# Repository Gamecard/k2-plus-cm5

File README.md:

# K2 Plus CM5 – Creality K2 Plus mit Upstream-Klipper auf einem Raspberry Pi CM5

> **ALPHA – Stand 24.10.2026 – Nachbau und Betrieb auf eigene Gefahr.** Bisher an **einem** Drucker erprobt
> (Stock-Firmware 1.1.7.0). Unsichere Punkte sind in den Dokumenten mit **ANNAHME** bzw. **offen** markiert.

Dieses Repo ersetzt das Upper-Board des Creality K2 Plus (Allwinner T113 in der Display-Einheit) durch einen
**Raspberry Pi Compute Module 5 (CM5)** mit **Upstream-Klipper**, Moonraker und Mainsail. Bridge-Board, Mainboard,
Düsen-Platine, Closed-Loop-Motoren, CFS-Box und Riemen-Module bleiben im Gerät und behalten ihre
**Creality-Firmware**. Eigene Klipper-Module (`pi-host/k2_*.py`) sprechen deren Protokolle und bilden die
geschlossenen Creality-Teile nach:

- RS485-Bus (`k2_485`) mit Motor-Init (`k2_motor`), CFS-Box (`k2_box`), Riemenspannung (`k2_belt`),
- Kraftsensor-Antastung PrTouch (`k2_prtouch`) und Beschleunigungssensor (`k2_lis2dw`) über die Düsen-MCU,
- Sicherheits- und Komfortfunktionen des Creality-Hosts (`k2_safety`, `k2_chamber`, `k2_limits`,
  `k2_nozzle_tempcomp`, `k2_heater_pid`, `k2_zalign`, `k2_resume`, `k2_dateipruefung`, `k2_konsole`, `k2_cfs_sensor`).

Der Protokoll-Nachbau in Python liegt in `nachbau/`; der Installer kopiert ihn auf dem Pi nach
`~/klipper/klippy/extras/k2_nachbau/`. Bedient wird über Mainsail im Browser, das Original-Touchdisplay bleibt ohne
Funktion.

## Ziel des Projekts

**Der Creality K2 Plus soll mit Upstream-Klipper auf einem Raspberry Pi CM5 laufen – mit allen Funktionen des
Druckers, einschließlich CFS-Mehrfarbbetrieb.**

| Teil | Im Projekt |
|---|---|
| Upper-Board (Allwinner T113 in der Display-Einheit) | **ersetzt** durch den CM5 mit Upstream-Klipper, Moonraker und Mainsail |
| Bridge-Board, Mainboard, Düsen-Platine, Closed-Loop-Motoren, CFS-Box, Riemen-Module | **bleiben im Gerät**, mit ihrer originalen, unveränderten Creality-Firmware |
| Original-Touchdisplay | ohne Funktion; Bedienung über Mainsail im Browser, später optional ein eigenes DSI-Display |

**Software:** Damit Upstream-Klipper mit den verbleibenden Creality-Teilen zusammenarbeitet, bringt das Projekt eigene
Klipper-Module mit, die mit diesen Teilen kommunizieren und die Aufgaben übernehmen, die bisher der Creality-Host
erledigt hat:

- RS485-Bus, Motoren, CFS-Box und Riemenspannung (`k2_485`, `k2_motor`, `k2_box`, `k2_belt`),
- Kraftsensor-Antastung und Beschleunigungssensor über die Düsen-MCU (`k2_prtouch`, `k2_lis2dw`),
- Sicherheits- und Komfortfunktionen wie Fahrgrenzen, Kammer-Überwachung und Wiedereinstieg ab einer Schicht
  (`k2_safety`, `k2_chamber`, `k2_limits`, `k2_resume` u. a.).

**Hardware:** Die eigene Trägerplatine „K2-CM5-Träger Alpha 1“ sitzt an den Befestigungspunkten des T113, nimmt das
Original-Flachkabel auf und wird aus den 24 V des Druckers versorgt. Sie bringt RS485, CAN, Strommessung,
Stromausfall-Erkennung und Kamera-USB mit. Aus dem Aufbau mit IO-Board, Breakout und Steckbrücken wird so ein
sauberer Einbau.

**Was das bringt:**

- ein offenes, aktuelles Klipper statt eines festen Hersteller-Stands – eigene Makros, eigene Module, Mainsail,
  Kameras nach Wahl;
- Erweiterungen, die mit der Original-Software nicht möglich sind, z. B. CAN für einen späteren Toolhead;
- eine offene, nachbaubare Lösung für andere Besitzer eines K2 Plus.

**Ausblick (Idee, nicht begonnen):** eine Version 3 der Platine, die zusätzlich das Bridge-Board ersetzt – eine
eigene Platine statt T113, Bridge-Board und Adapter.

Das Projekt ist **Alpha**: Nachbau und Betrieb auf eigene Gefahr, Hardware nur für Testzwecke und nicht kommerziell
(CC BY-NC-SA 4.0, siehe [Lizenzen](#lizenzen)).

## Status

| Teil | Stand |
|---|---|
| Software (`pi-host/`, `nachbau/`) | läuft auf **CM5 + Waveshare CM5-IO-BASE-B** mit Breakout-Verdrahtung am Original-Flachkabel. Am Gerät erprobt (22.–23.10.2026): Klipper „ready“ mit beiden MCUs, Motor-Init, X/Y-Homing, Kraftsensor-Antastung, Bett ausrichten und Mesh, PID, Input Shaper, Riemenspannung, CFS-Laden/-Entladen/-Wechsel, einfarbiger Druck und ein Mehrfarbdruck (Creality-Print-7-Datei, 182 Wechsel) |
| Offen | u. a. Dual-Z-Lichtschranken, einige Druckfälle (PAUSE/RESUME, Restmaterial, Stall-Überwachung), `k2-bootstart` am Gerät – siehe [`SCHNELLSTART-K2-PLUS.md`](SCHNELLSTART-K2-PLUS.md) §9 und [`PI-INBETRIEBNAHME.md`](PI-INBETRIEBNAHME.md) Anhang D |
| Trägerplatine „K2-CM5-Träger Alpha 1“ (`hardware/k2-pi-cm5-traeger/`) | gefertigt, **seit 09.11.2026 an einem Drucker in Betrieb** (RS485, beide MCUs, CFS, Strommessung, CAN-Controller, Stromausfall-Erkennung, Kamera-USB geprüft); offen: DSI-Display, Ethernet, CAN mit Teilnehmer, Dauerlast-Temperatur – Details in der [Platinen-README](hardware/k2-pi-cm5-traeger/README.md) |
| Softwarepaket zur Trägerplatine (`pi-host/traeger-alpha1/`) | auf dem Träger installiert und **in Betrieb** (seit 09.11.2026) |

## Zwei Aufbauwege

**A – CM5 + IO-Board + Verdrahtung (heute erprobt).** CM5 auf einem IO-Board mit 40-Pol-Leiste (bei uns Waveshare
CM5-IO-BASE-B), FFC-Breakout am Original-Flachkabel, vier UART-Leitungen mit 1 kΩ, USB-RS485-Adapter für den Bus.

1. [`SCHNELLSTART-K2-PLUS.md`](SCHNELLSTART-K2-PLUS.md) – der Weg vom unveränderten Drucker bis zum Druck, kurz gefasst;
   Verkabelung in Abschnitt 3, Verdrahtungsbild: [`bilder/verdrahtung-weg-a.png`](bilder/verdrahtung-weg-a.png).
2. [`PI-ANSCHLUSS-LOWERBOARD.md`](PI-ANSCHLUSS-LOWERBOARD.md) – Bridge-Board, J14-/J22-Belegung, Messprotokoll.
3. [`PI-INBETRIEBNAHME.md`](PI-INBETRIEBNAHME.md) – Fahrplan Phase 0–12 mit Erwartungswerten, Not-Aus-Stufen,
   Schalterstand und Rückweg zum Original.

**B – Trägerplatine (Alpha, seit 09.11.2026 an einem Drucker in Betrieb).** Der Träger sitzt an den Befestigungspunkten des T113, trägt den CM5
direkt und nimmt das Original-Flachkabel auf; versorgt wird er aus den 24 V des Druckers. Breakout, Steckbrücken und
USB-RS485-Adapter entfallen.

1. [`hardware/k2-pi-cm5-traeger/README.md`](hardware/k2-pi-cm5-traeger/README.md) – Platine, Einkauf, Aufbau und Inbetriebnahme
   ([`AUFBAU-UND-INBETRIEBNAHME.md`](hardware/k2-pi-cm5-traeger/AUFBAU-UND-INBETRIEBNAHME.md)).
2. [`pi-host/traeger-alpha1/README-traeger-alpha1.md`](pi-host/traeger-alpha1/README-traeger-alpha1.md) –
   Softwarepaket und Umstieg (RS485 über UART0, CAN, Stromausfall-Wächter, `config.txt`).

## Einstieg

Mit [`SCHNELLSTART-K2-PLUS.md`](SCHNELLSTART-K2-PLUS.md) anfangen. Vor dem Umbau am **laufenden Original** die
Kalibrierwerte, die Materialdatenbank und das Düsenmaterial sichern (Schnellstart §2) – diese Dateien enthalten
Geräte- und Cloud-Kennungen und gehören **nie** in ein Repo oder Paket.

Kurzform der Installation (Einzelheiten: [`pi-host/install/README.md`](pi-host/install/README.md)):

```bash
git clone https://github.com/Gamecard/k2-plus-cm5.git
cd k2-plus-cm5
pi-host/install/pack.sh --tests --ohne-dicts      # oder --dicts ORDNER mit den MCU-Dictionaries der Creality-Firmware
scp lokal/pi-paket/k2-pi-paket-<datum>.tar.gz pi@<pi-ip>:~
ssh pi@<pi-ip>
tar xzf k2-pi-paket-<datum>.tar.gz && cd k2-pi-paket-<datum>
./install.sh --printer-cfg-ersetzen --bewegung-gesperrt   # weitere Optionen: Schnellstart §4
```

Der Ordner `lokal/` ist git-ignoriert und nimmt alles Gerätebezogene auf (gebaute Pakete, MCU-Dictionaries, optional
eine eigene Leak-Muster-Liste für `pack.sh`).

## Ordnerübersicht

| Pfad | Inhalt |
|---|---|
| [`SCHNELLSTART-K2-PLUS.md`](SCHNELLSTART-K2-PLUS.md) | Einstieg: Voraussetzungen, Sichern, Verkabelung, Installation, Kalibrierung, Slicer, Betrieb, Rückweg |
| [`PI-ANSCHLUSS-LOWERBOARD.md`](PI-ANSCHLUSS-LOWERBOARD.md) | Anschluss an Bridge- und Mainboard, Messwerte, Belegungen |
| [`PI-INBETRIEBNAHME.md`](PI-INBETRIEBNAHME.md) | Fahrplan der Inbetriebnahme (Phase 0–12, Anhänge Rückweg, Protokoll, Variante A) |
| [`BOOTSTART-WERKZEUG.md`](BOOTSTART-WERKZEUG.md) | `k2-bootstart`: Geräte aus dem Bootloader in die App starten (Gerätetest offen, Standard aus) |
| [`pi-host/`](pi-host/README.md) | Klipper-Module `k2_*.py`, Offline-Tests `test_k2_*.py`, je Modul eine `README-k2_*.md` |
| [`pi-host/config-pi/`](pi-host/config-pi/README.md) | Klipper-Konfiguration des K2 Plus (`printer.cfg`, Makros, Module, Homing, Z-Ausrichtung) mit Bedienhinweisen |
| [`pi-host/install/`](pi-host/install/README.md) | `pack.sh` (Paket bauen), `install.sh`/`uninstall.sh`, `k2-identify.py`, `k2-bootstart.py`, Start-Wächter, Creality-Brücke, Web-Anpassungen, Tests |
| [`pi-host/traeger-alpha1/`](pi-host/traeger-alpha1/README-traeger-alpha1.md) | Softwarepaket für die Trägerplatine (am Träger in Betrieb) |
| `nachbau/` | Python-Nachbau der Creality-Protokolle (RS485-Bus, CFS-Box, Motoren, Adressvergabe, Bootstart, Spülen, Materialdatenbank); `ref-hi/` = Testvektoren |
| [`hardware/k2-pi-cm5-traeger/`](hardware/k2-pi-cm5-traeger/README.md) | Trägerplatine Alpha 1: Generator, KiCad-Projekt, Fertigungsdaten in `ausgabe/`, Bestell- und Aufbauanleitung |
| [`hardware/LIZENZ-UND-HAFTUNG.md`](hardware/LIZENZ-UND-HAFTUNG.md) | Lizenz (CC BY-NC-SA 4.0) und Haftungsausschluss der Hardware |
| `belt_mdl-live.py` | Creality-Original des Riemenmoduls (GPLv3), Vergleichsreferenz für `pi-host/test_k2_belt.py` |
| [`NOTICES.md`](NOTICES.md), [`LICENSE`](LICENSE) | Herkunfts- und Lizenzhinweise, GPL-3.0 |

## Sicherheit und Verbote

**Was dieses Projekt nie tut – und was auch Nutzer nicht tun sollten:**

- **Keine Motor-Kalibrierung:** Die Motor-Schreibbefehle **0x03** (Encoder), **0x04** (Elektrik-Offset) und
  **0x07** (Flash-Parameter) sind im Sendeschutz gesperrt. Den Sendeschutz nicht umgehen.
- **Kein Bootloader-Einstieg und kein Flashen** von Motoren, CFS, Riemen-Modulen oder MCUs (u. a. `FF 0B [00]`,
  fun 0xF0 Sub 01, `mcu_util`-/`mcu_util_485`-/SWD-Wege) und **kein CFS-DB-Erase** (`F0 [06]`). `k2-bootstart`
  startet nur, es aktualisiert nie.
- **Main-MCU (Lower-Board) und Düsen-MCU NICHT mit generischem Klipper flashen.** Die Module sind auf die originale
  Creality-MCU-Firmware abgestimmt (erprobt: `1.1.0.48-293-g493f9a0f`). Weil nichts geflasht wird, bleibt der
  Rückweg zum Original jederzeit möglich (Flachkabel zurück an das T113).

**Elektrik und Mechanik:**

- Arbeiten an 24 V und an der Drucker-Elektronik erfolgen **auf eigene Gefahr**. Auf dem Bridge-Board liegen
  RS232-Pegel von ±5,5 V, die Pi-UARTs vertragen höchstens 3,3 V. Stecken und Ziehen nur bei ausgeschaltetem Drucker
  **und** Pi, GND zuerst. Die 5-V-Stifte des Breakouts nie an den Pi.
- Ab der Bewegungsfreigabe kann der Kopf in den Rahmen, die Düse ins Bett fahren: immer eine Person am Netzschalter,
  Bett leer. Bus-Schreiben und Bewegung sind ab Werk gesperrt (`allow_write`/`allow_move`) und werden schrittweise
  nach dem Fahrplan freigegeben.
- Die Heizungen gehen **nie automatisch** aus (`[idle_timeout]` wie Stock): nach jedem Heizschritt
  `TURN_OFF_HEATERS`.
- Der Eingriff kann Garantie- bzw. Gewährleistungsansprüche gegenüber dem Hersteller beeinträchtigen. Es gibt keine
  Gewährleistung und keinen Support.

## Lizenzen

- **Software** (`pi-host/`, `nachbau/`, Skripte, Dokumentation außerhalb von `hardware/`): **GPL-3.0-or-later**
  ([`LICENSE`](LICENSE)). Die Module sind Erweiterungen für Klipper (GPL-3.0).
- `belt_mdl-live.py` ist ein **Creality-Original** unter **GPLv3** (Lizenzhinweis im Dateikopf).
- `nachbau/ref-hi/` stammt aus **gitstonelabs/creality-cfs-klipper** (GPL-3.0).
- **Hardware** (`hardware/`): **CC BY-NC-SA 4.0**, Alpha, nur für Testzwecke, keine kommerzielle Nutzung –
  Einzelheiten und Haftungsausschluss in [`hardware/LIZENZ-UND-HAFTUNG.md`](hardware/LIZENZ-UND-HAFTUNG.md).
- Weitere Herkunftsangaben: [`NOTICES.md`](NOTICES.md).

## Hinweis

Dieses Projekt ist unabhängig und **nicht mit Creality verbunden**. „Creality“, „K2 Plus“, „CFS“, „Raspberry Pi“
und alle anderen genannten Marken gehören ihren jeweiligen Inhabern.

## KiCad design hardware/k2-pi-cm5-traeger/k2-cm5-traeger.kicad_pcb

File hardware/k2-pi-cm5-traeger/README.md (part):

# K2-CM5-Träger Alpha 1 (Weg B) – Layout-Entwurf (23.10.2026, Umbau 24.10.2026)

> **ALPHA – NUR FÜR TESTZWECKE – NICHT FÜR DEN KOMMERZIELLEN EINSATZ – NUTZUNG AUF EIGENE GEFAHR.**
> Lizenz und Haftungsausschluss: siehe [`../LIZENZ-UND-HAFTUNG.md`](../LIZENZ-UND-HAFTUNG.md).

> **Status (11.11.2026): Alpha 1 – gefertigt (JLC), seit 09.11.2026 an einem Drucker in Betrieb.** Layout
> DRC/ERC 0 Fehler. Am Gerät geprüft: Versorgung aus den 24 V des Druckers, beide MCUs über das Original-Flachkabel, RS485 über den Treiber der Platine (Motor-Init aller fünf Motoren, CFS-Box), Strommessung (INA226 24 V und 5 V), CAN-Controller erkannt, Stromausfall-Erkennung, beide Kamera-USB, erste Drucke mit CFS-Wechsel. **Offen:** DSI-Display (Hintergrundlicht/Touch antworten nicht, Ursache offen), Ethernet, CAN mit angeschlossenem Teilnehmer, CM5-Temperatur unter Dauerlast (passiver Kühler, bisher 63–66 °C, keine Drosselung).
> Weitere Punkte: [Offene Punkte](#offene-punkte) am Ende.

> **Unterlagen:** [Fertigungshinweise](#fertigungshinweise-leiterplatte-und-bestückung) · [`EINKAUFSLISTE.md`](EINKAUFSLISTE.md) (alles außer JLC) · [`AUFBAU-UND-INBETRIEBNAHME.md`](AUFBAU-UND-INBETRIEBNAHME.md)
> (Messungen in 12 Etappen) · [`KOMPROMISSE-UND-OFFENE-PUNKTE.md`](KOMPROMISSE-UND-OFFENE-PUNKTE.md) · Software:
> [`../../pi-host/traeger-alpha1/README-traeger-alpha1.md`](../../pi-host/traeger-alpha1/README-traeger-alpha1.md).

> **Umbau 24.10.2026 (Nutzerwunsch):** 24-V-Eingang **J7 an Kante A** (über J1, Kabel von links wie beim Flachkabel),
> **J9b/J11 stehend** (JST GH Top entry), **tauschbare Eingangssicherung** (Littelfuse 157 mit Nano²-Sicherung),
> **Stromausfall-Erkennung** (INA226-ALERT → GPIO27).

> **Weg A (Entscheidung 24.10.2026):** **J9 (Toolhead 24 V + CAN) entfällt** samt eFuse, INA226 0x44 und dem
> 24-V-Stamm quer über die Platine. Der Toolhead bekommt seine 24 V **direkt vom Drucker-Netzteil** (eigene Kabelsicherung
> ≈ 5 A, siehe „Toolhead-Versorgung“), CAN läuft über **J9b**. Eingangssicherung **F1 jetzt 3 A** (Platine braucht ≈ 10–15 W).
> Die Platzhalter-Quader der 3D-Ansicht sind, wo möglich, durch echte Modelle ersetzt (siehe „3D-Modelle und Lizenzen“).

Konzept und Begründungen: [`KONZEPT.md`](KONZEPT.md) (inkl. Tabelle „Entscheidungen“).

## Zweck

Der Träger ersetzt das T113-Upper-Board des K2 Plus an dessen vier Befestigungspunkten. Er trägt ein **Raspberry Pi
Compute Module 5 (CM5)** direkt (zwei 100-pol. Steckverbinder, 1,5 mm Bauhöhe) – ohne IO-Board. Das Original-Flachkabel
vom Bridge-Board steckt in **J1** (Lage wie CON2 der T113). Der Träger versorgt den CM5 selbst aus den 24 V des Druckers.

## Funktionen

| Block | Umsetzung | Anschluss / CM5-Pins |
|---|---|---|
| Flachkabel J1 | 50-pol. FPC 0,5 mm (XUNPU FPC-05FB-50PH20), Kante A; J1-Pin n = Breakout-Nummer n (CON2 = 51 − Breakout) | Breakout 45–50 = Drucker-5V (**nie** am CM5-5V), 1/2 + 4/5 Ethernet |
| UART2 / UART4 | je 1 kΩ + ESD (SRV05-4) + Ioff-Puffer SN74LVC1G125 (5,5-V-tolerant) | Breakout 26/28 (UART2), 30/32 (UART4); CM5 54/34, 31/28 |
| RS485 | THVD1450 an UART0, DE = GPIO17; Ruhevorspannung (JP2/JP3) und 120 Ω (JP_485_TERM) schaltbar | Breakout 19 = B, 20 = A; CM5 55/51/50 |
| RS485-Abgriff J11 | JST GH 3-pol. **stehend** (BM03B-GHS-TBT, LCSC C161691), A/B/GND parallel zum Bus, ESD | Kante D |
| CAN | MCP2518FD (SPI0, INT = GPIO25) + SN65HVD230, ESD NUP2105 | CM5 44/40/38/39/41 |
| **CAN-Anschluss J9b** | JST GH 3-pol. **stehend** (BM03B-GHS-TBT, LCSC C161691): CANH, CANL, GND (kein 24 V) – seit Weg A **der** CAN-Anschluss für ein späteres Toolhead-Board (24 V dafür direkt vom Netzteil) | **Kante B** (zwischen L-Spule und L2) |
| CAN-Abschluss | 120 Ω über Stiftleiste **JP_CAN_TERM** („CAN 120R“), Jumper **ab Werk gesteckt** | Kante D unten rechts |
| 24-V-Eingang J7 | XT30PW-M liegend (Stecköffnung nach links), **tauschbare Sicherung F1** (Littelfuse 157, **3 A**), TVS D8, Shunt R23 5 mΩ + INA226 0x40 direkt dahinter (unten, unter J7), 24-V-Stamm auf L3 nur noch bis zum Wandler | **Kante A oben** (über J1) |
| Stromausfall-Erkennung | INA226 0x40 ALERT (open drain) → **PWR_FAIL_N** → **GPIO27 (CM5-Pin 48)**, 10 k Pull-up R50, Messpad TP12 | siehe unten |
| 5,2 V für den CM5 | LMR51450 (5 A, Spule FXL0630) → Power-Mux TPS2121 → Shunt 10 mΩ (INA226 0x41) → CM5 77–87 | – |
| Notfall-USB-C J10 | stehend, Kante B bei L1: USB-OTG (CM5 103/105), CC 94/96 (5,1 k als Bestückoption), nRPIBOOT per Jumper **JP_BOOT**, 5 V über TPS2121, ESD USBLC6 | USB_OTG_ID 101 offen |
| Kamera-/Hub-USB | 90 Ω, CM5 134/136 bzw. 163/165 → J1 37/38 bzw. 34/35, ESD | – |
| Ethernet | CM5-Paar 0 (12/10) und 1 (4/6) → eigener Übertrager H1102NL → J1 1/2 und 4/5, Mittelanzapfung/Bob-Smith | – |
| **DSI-Display J12** | **bestückt**: 22-pol. FPC 0,5 mm Hirose FH12-22S-0.5SH(55), Belegung wie Raspberry Pi 5 / CM-IO; **MIPI1 = DSI1**, 2 Datenlanes + Takt | **Kante C** (wie CON1 der T113) |
| DSI-3,3 V | eigener Abwärtswandler TLV62569 (2 A) aus CM5-5V, EN an CM5-3,3V | J12 Pin 22 |
| LEDs | 3V3, nACT (21), Ethernet nLED3/nLED2 (15/17), D10 „Flachkabel richtig“ (Drucker-5V) | Kante D |
| Messpunkte | 5V, 3V3, RUN (99), BOOT (93), PWR (92), GND; unten 24 V, BR_5V, PWR_FAIL (TP12) | Kante D bzw. unten |
| Sonstiges | GPIO_VREF (78) an 3,3 V, EEPROM_nWP (20) offen; **GPIO6 (30) und GPIO26 (24) frei** (seit Weg A, im Schaltplan als „frei“ vermerkt) | – |

## DSI-Display (Nachtrag 2/3)

- Ziel-Display: **Waveshare 4.3inch DSI LCD** (800 × 480, Touch Goodix über I2C im Kabel, 3,3 V ≈ 1,2 W, Kabel 22 → 15 pol.).
  Für Pi 5/CM5 ist **Rev 2.2** des Displays nötig (Tabelle „Entscheidungen“ in `KONZEPT.md`).
- Stecker **J12 an Kante C**, senkrecht entlang der Kante zwischen den Bohrungen L2 und L4, Öffnung zur Kante, Kabel geht
  nach außen ab – dort, wo an der T113 der Display-Stecker **CON1** sitzt (am 23.10.2026 bestätigt).
- Kontaktseite und Pin 1 wie Raspberry Pi 5 bzw. CM-IO-Board: Es ist **derselbe Stecker (Hirose FH12-22S-0.5SH)** wie auf dem
  CM4-IO-Board (KiCad-Designdaten von Raspberry Pi), Pin 1 liegt am südlichen Ende (Richtung L4). Ein Pi-5-Displaykabel passt
  ohne Verdrehen.
- Belegung (wie Pi 5 / CM-IO, 22-pol.):

| Pin | Signal | CM5-Pin | Pin | Signal | CM5-Pin |
|---|---|---|---|---|---|
| 1 | GND | – | 12 | D2_P | nicht verlegt (offen) |
| 2 | D0_N | 175 (MIPI1_D0_N) | 13 | GND | – |
| 3 | D0_P | 177 | 14 | D3_N | nicht verlegt (offen) |
| 4 | GND | – | 15 | D3_P | nicht verlegt (offen) |
| 5 | D1_N | 181 | 16 | GND | – |
| 6 | D1_P | 183 | 17 | CAM_GPIO0 | 97 |
| 7 | GND | – | 18 | CAM_GPIO1 | 100 |
| 8 | C_N | 187 (MIPI1_C_N) | 19 | GND | – |
| 9 | C_P | 189 | 20 | SCL | 35 (ID_SC), 2,2 k nach 3,3 V |
| 10 | GND | – | 21 | SDA | 36 (ID_SD), 2,2 k nach 3,3 V |
| 11 | D2_N | nicht verlegt (offen) | 22 | 3,3 V | DSI-Wandler U14 |

- Port-Wahl: **MIPI1 (DSI1)**, weil seine Pins (175–189) in Reihe B direkt zur rechten Kante zeigen; die I2C von MIPI1 liegt
  laut CM5-Datenblatt auf **ID_SD/ID_SC (Pin 36/35)**. Software: `dtoverlay=vc4-kms-dsi-7inch` (= DSI1). Für DSI0 wäre es
  `dtoverlay=vc4-kms-dsi-7inch,dsi0` – auf diesem Träger **nicht** verdrahtet.
- Paare: Takt, D0, D1 als **100-Ω-Paare 0,20/0,20 mm** nur auf L1 über der GND-Lage, ohne Via; Länge je Leitung
  **49,870 mm**, Abweichung im Paar und zwischen den Lanes < 0,001 mm (verschachtelte Paarbeulen + Innenabgleich).
  D2/D3 sind nicht verlegt – das Waveshare-Kabel (15-pol. Ende) führt ohnehin nur 2 Lanes.
- **3,3-V-Budget:** eigener Abwärtswandler **TLV62569** (2 A, 1,5 MHz, 2,2 µH, 2 × 22 µF) aus CM5-5V; Bedarf des Displays
  ≈ 1,2 W ≈ 0,36 A ≥ 0,5 A Vorgabe ✓ (2 A Reserve). Er belastet die 5,2-V-Schiene mit ≈ 0,3 A. Die 3,3-V-Schiene des CM5
  wird nicht belastet (sie schaltet nur EN, damit das Display nicht in einen ausgeschalteten CM5 zurückspeist).

## Mechanik und Lage

Draufsicht von oben, Ursprung linke obere Ecke, x nach rechts, y nach unten, Maße in mm.

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
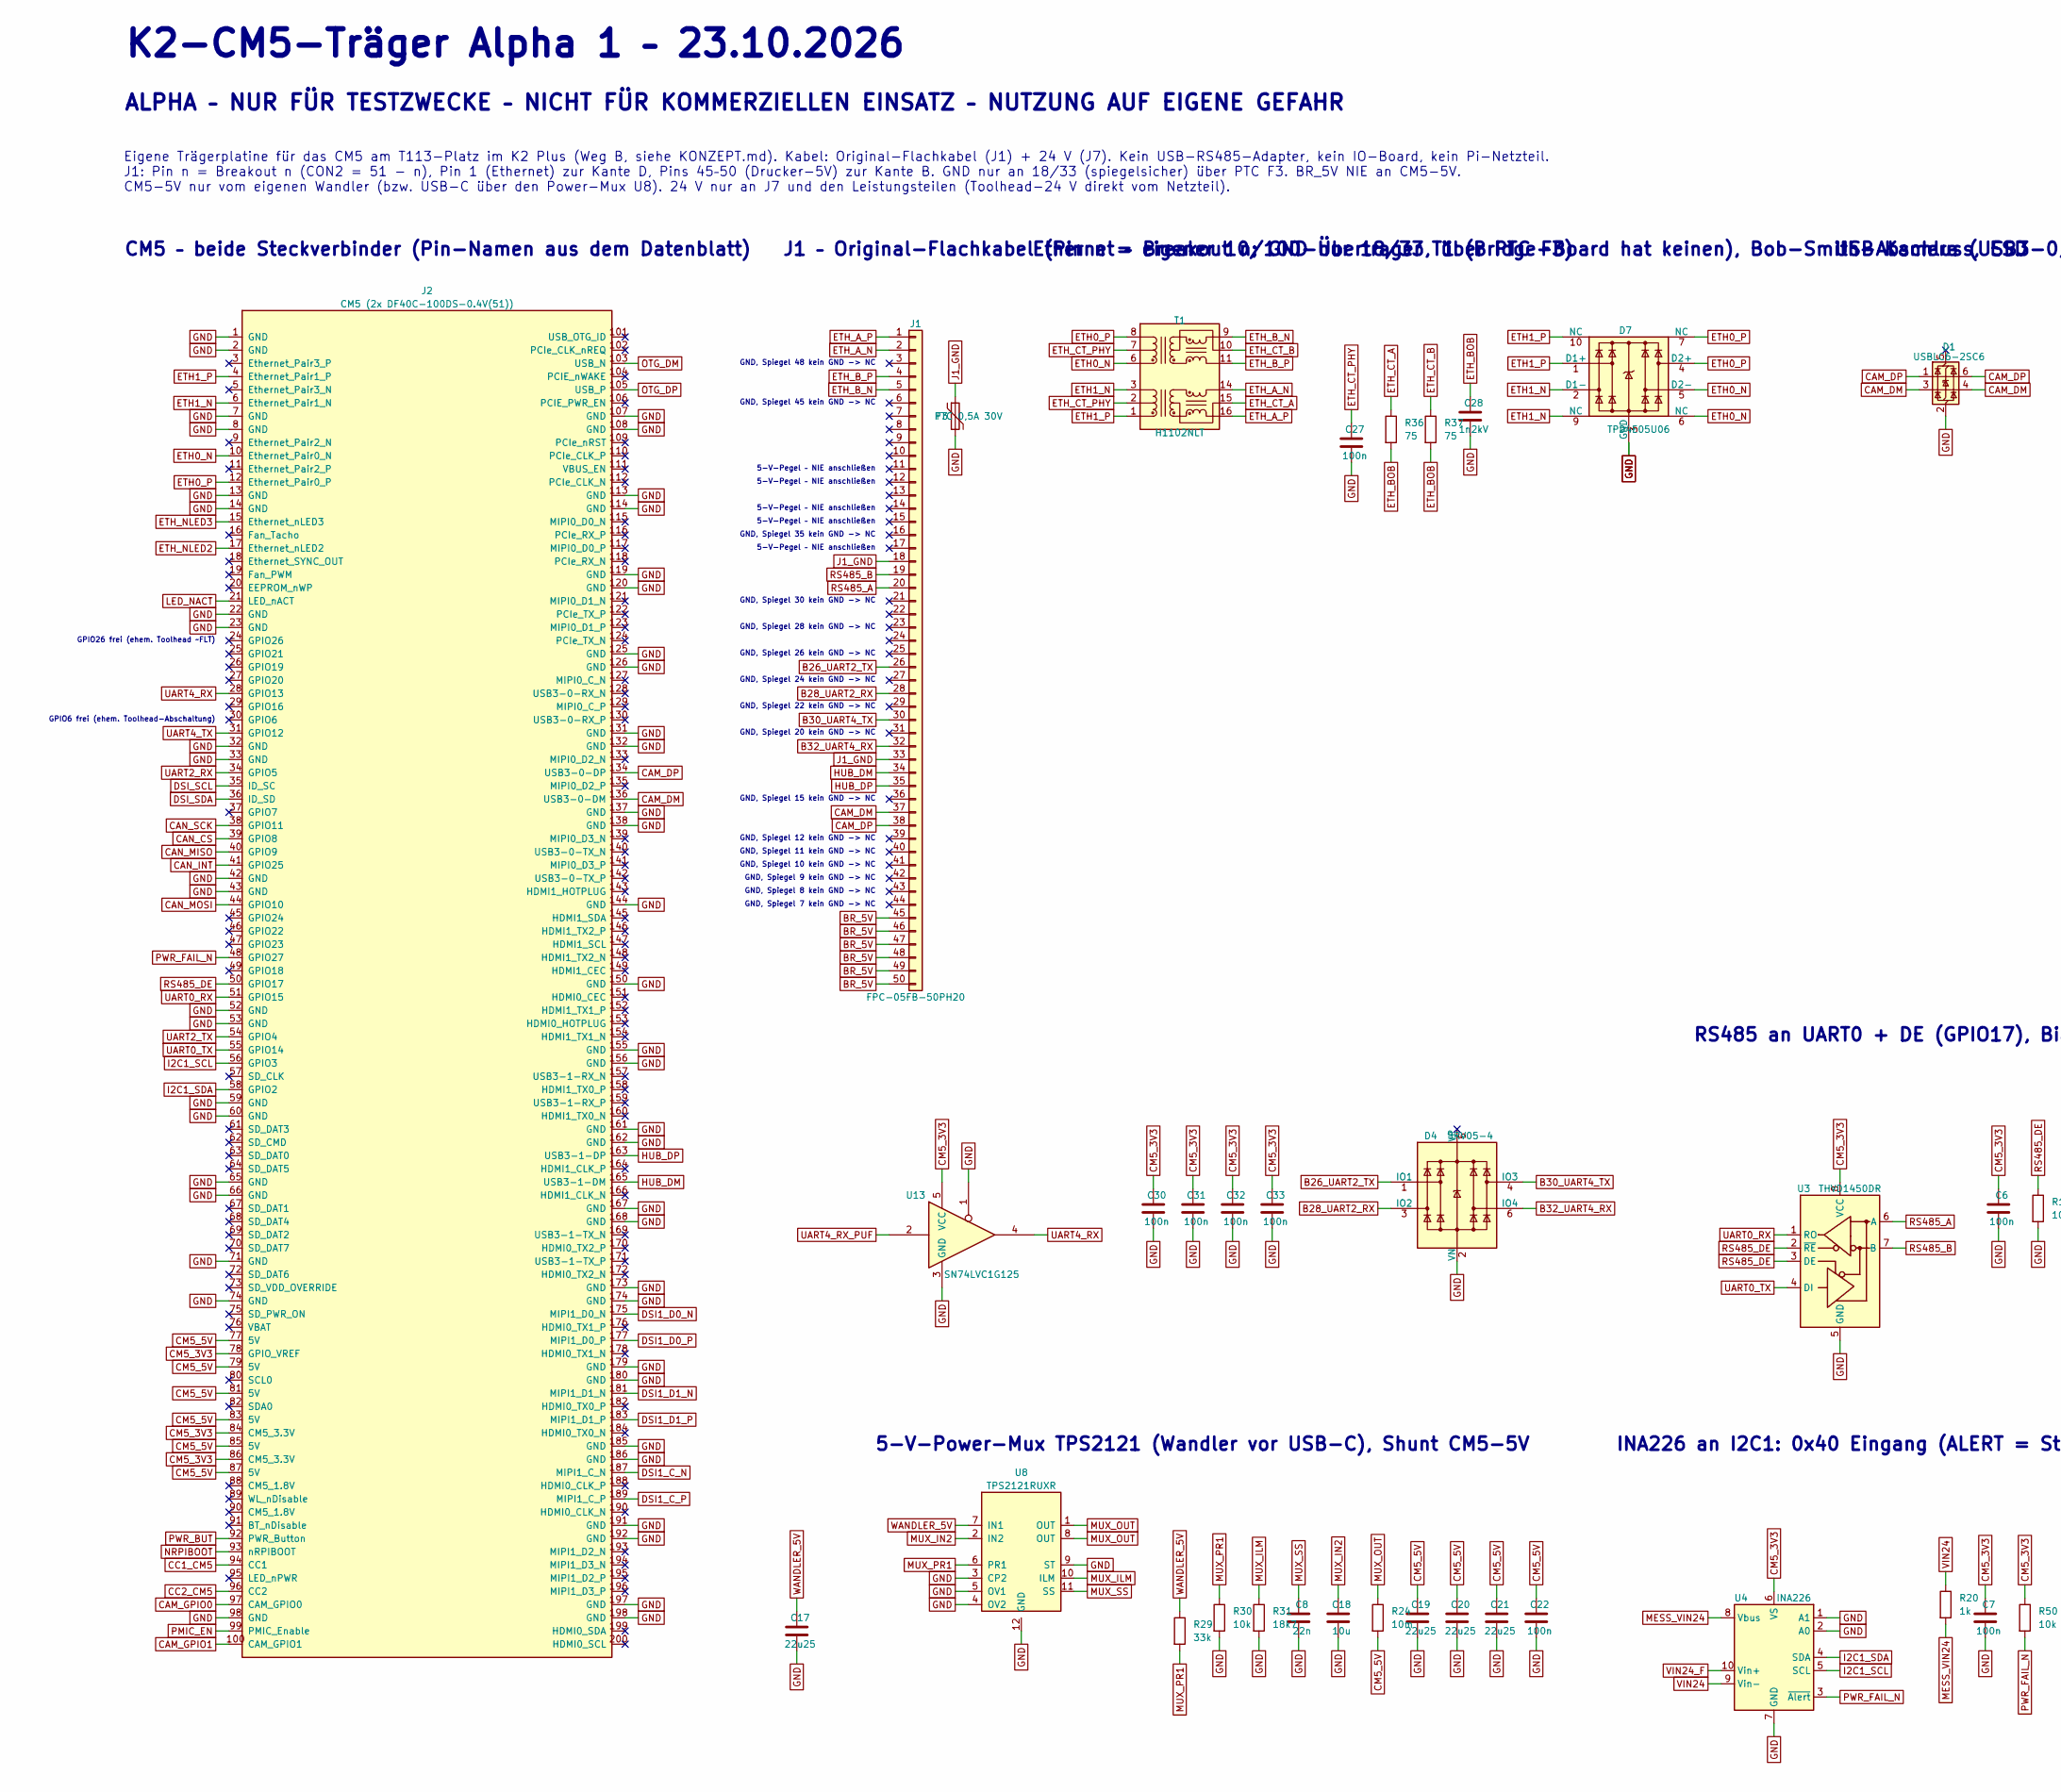
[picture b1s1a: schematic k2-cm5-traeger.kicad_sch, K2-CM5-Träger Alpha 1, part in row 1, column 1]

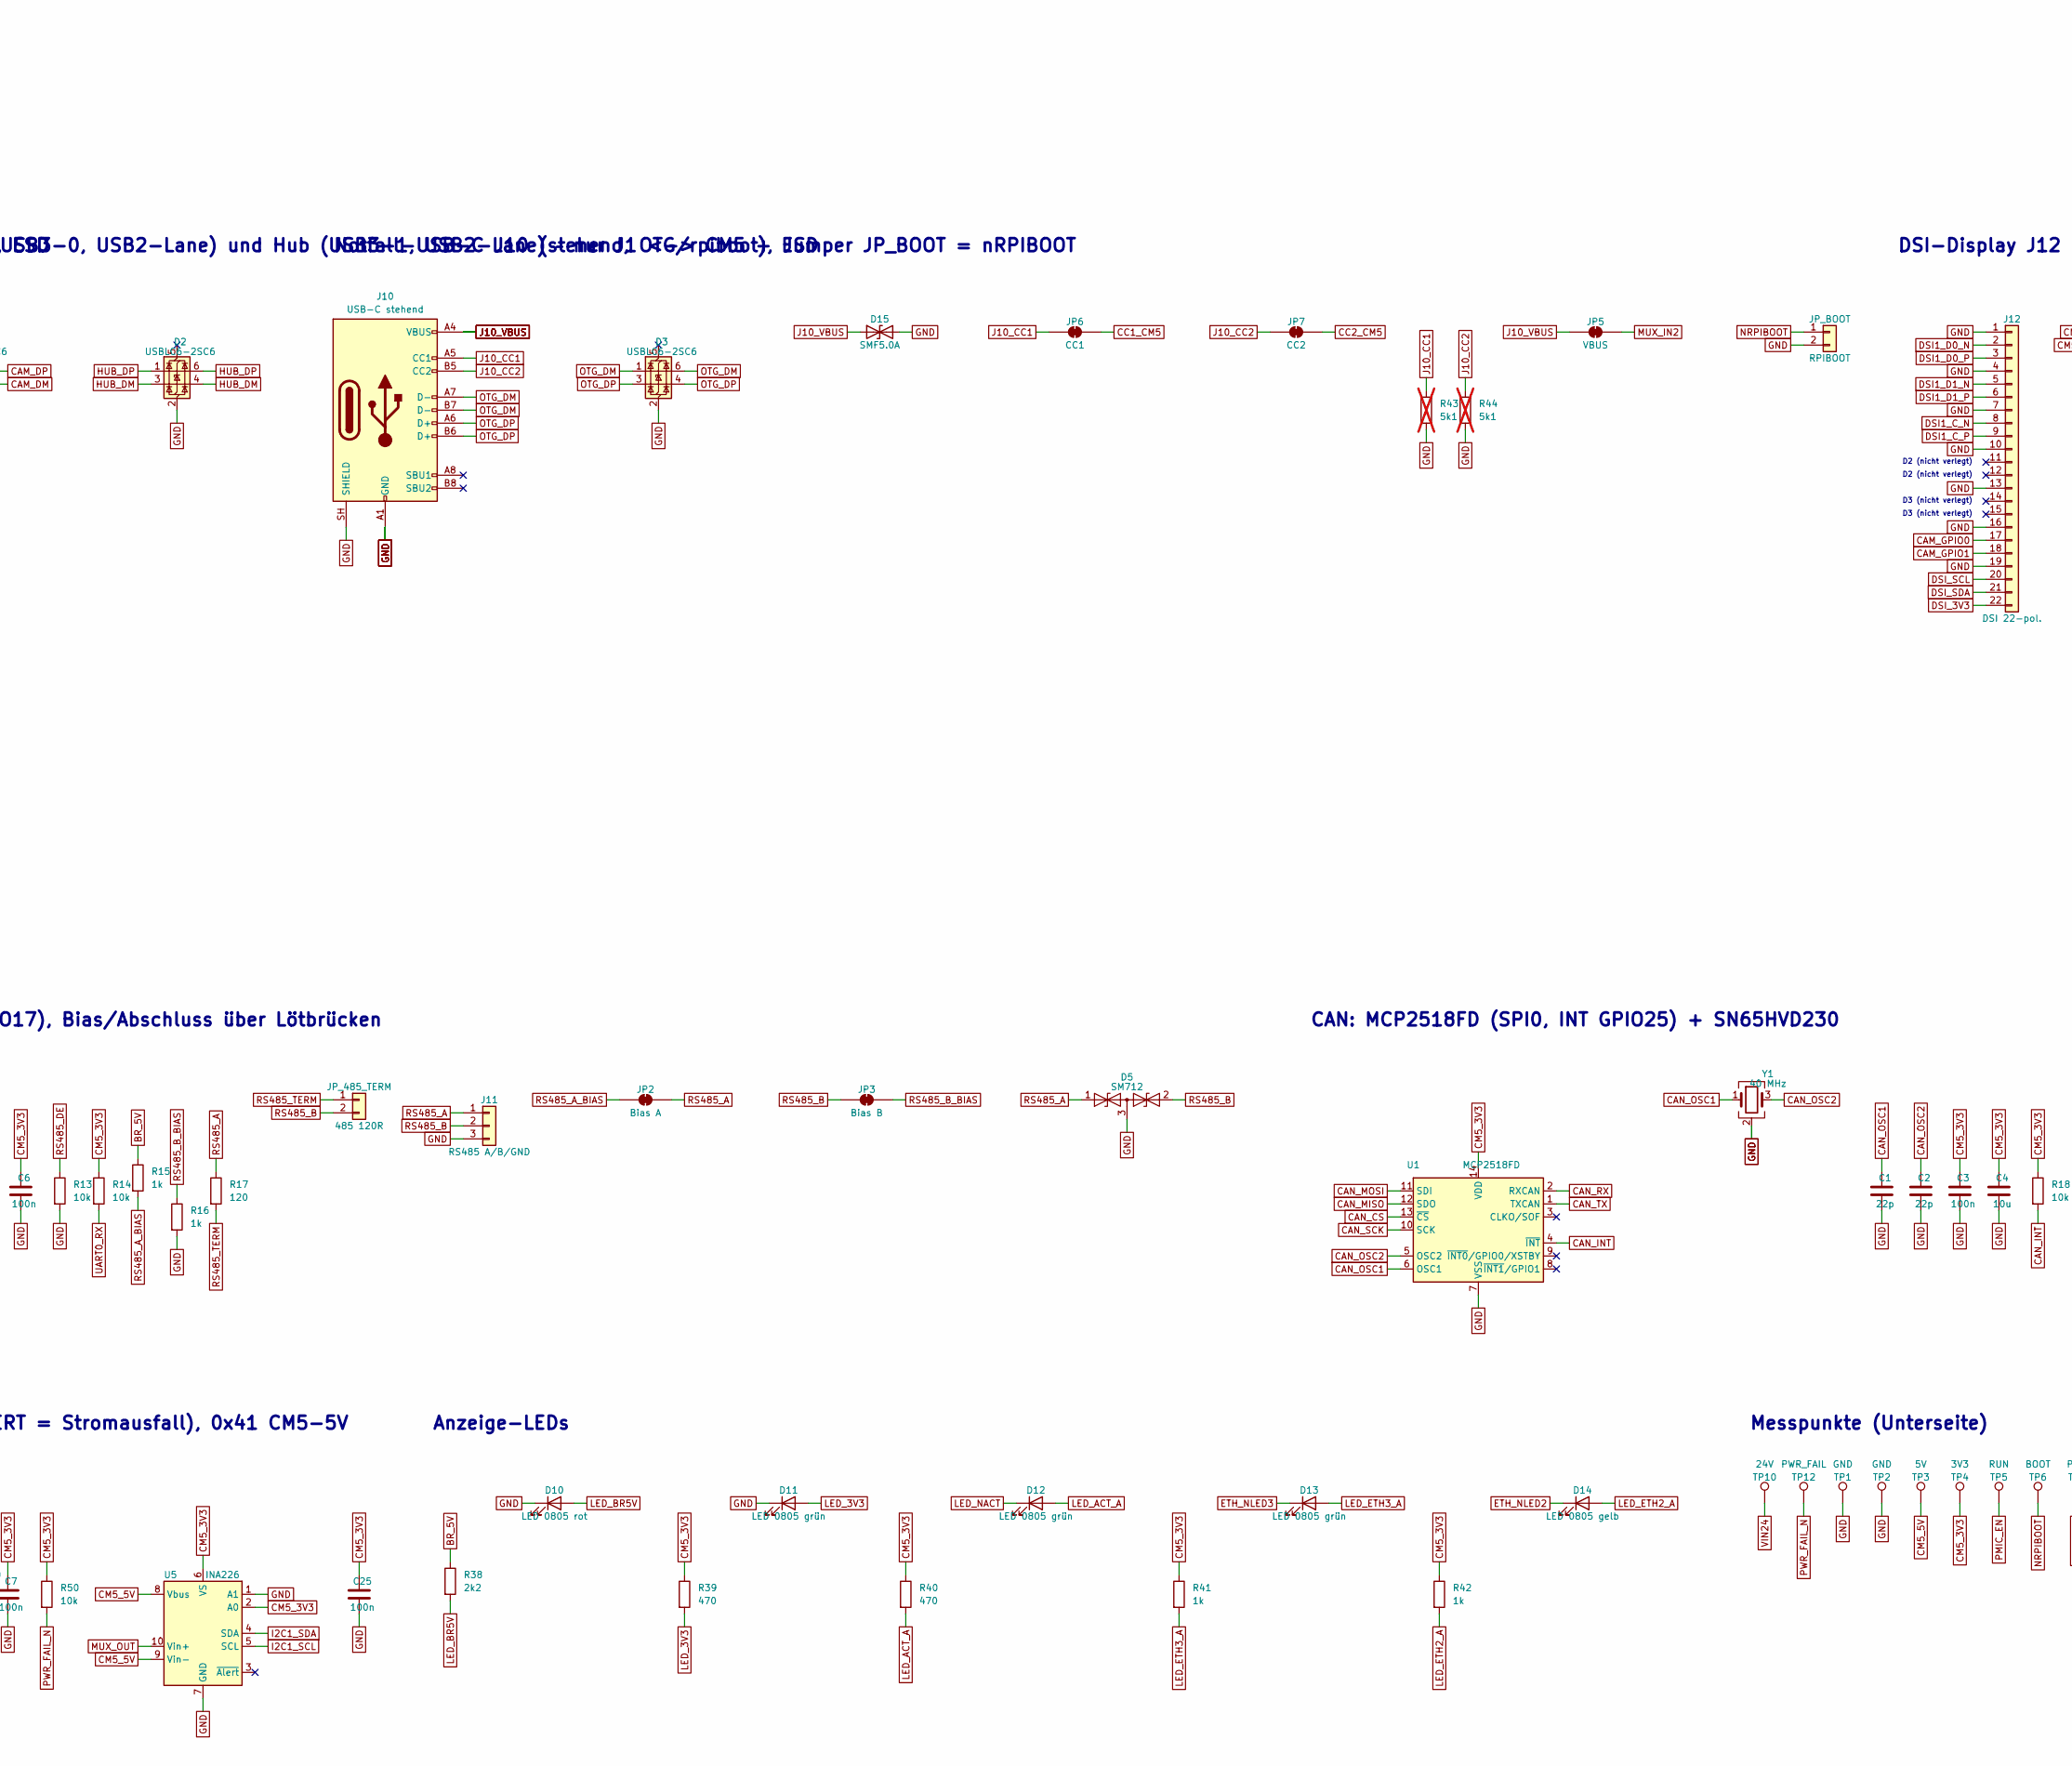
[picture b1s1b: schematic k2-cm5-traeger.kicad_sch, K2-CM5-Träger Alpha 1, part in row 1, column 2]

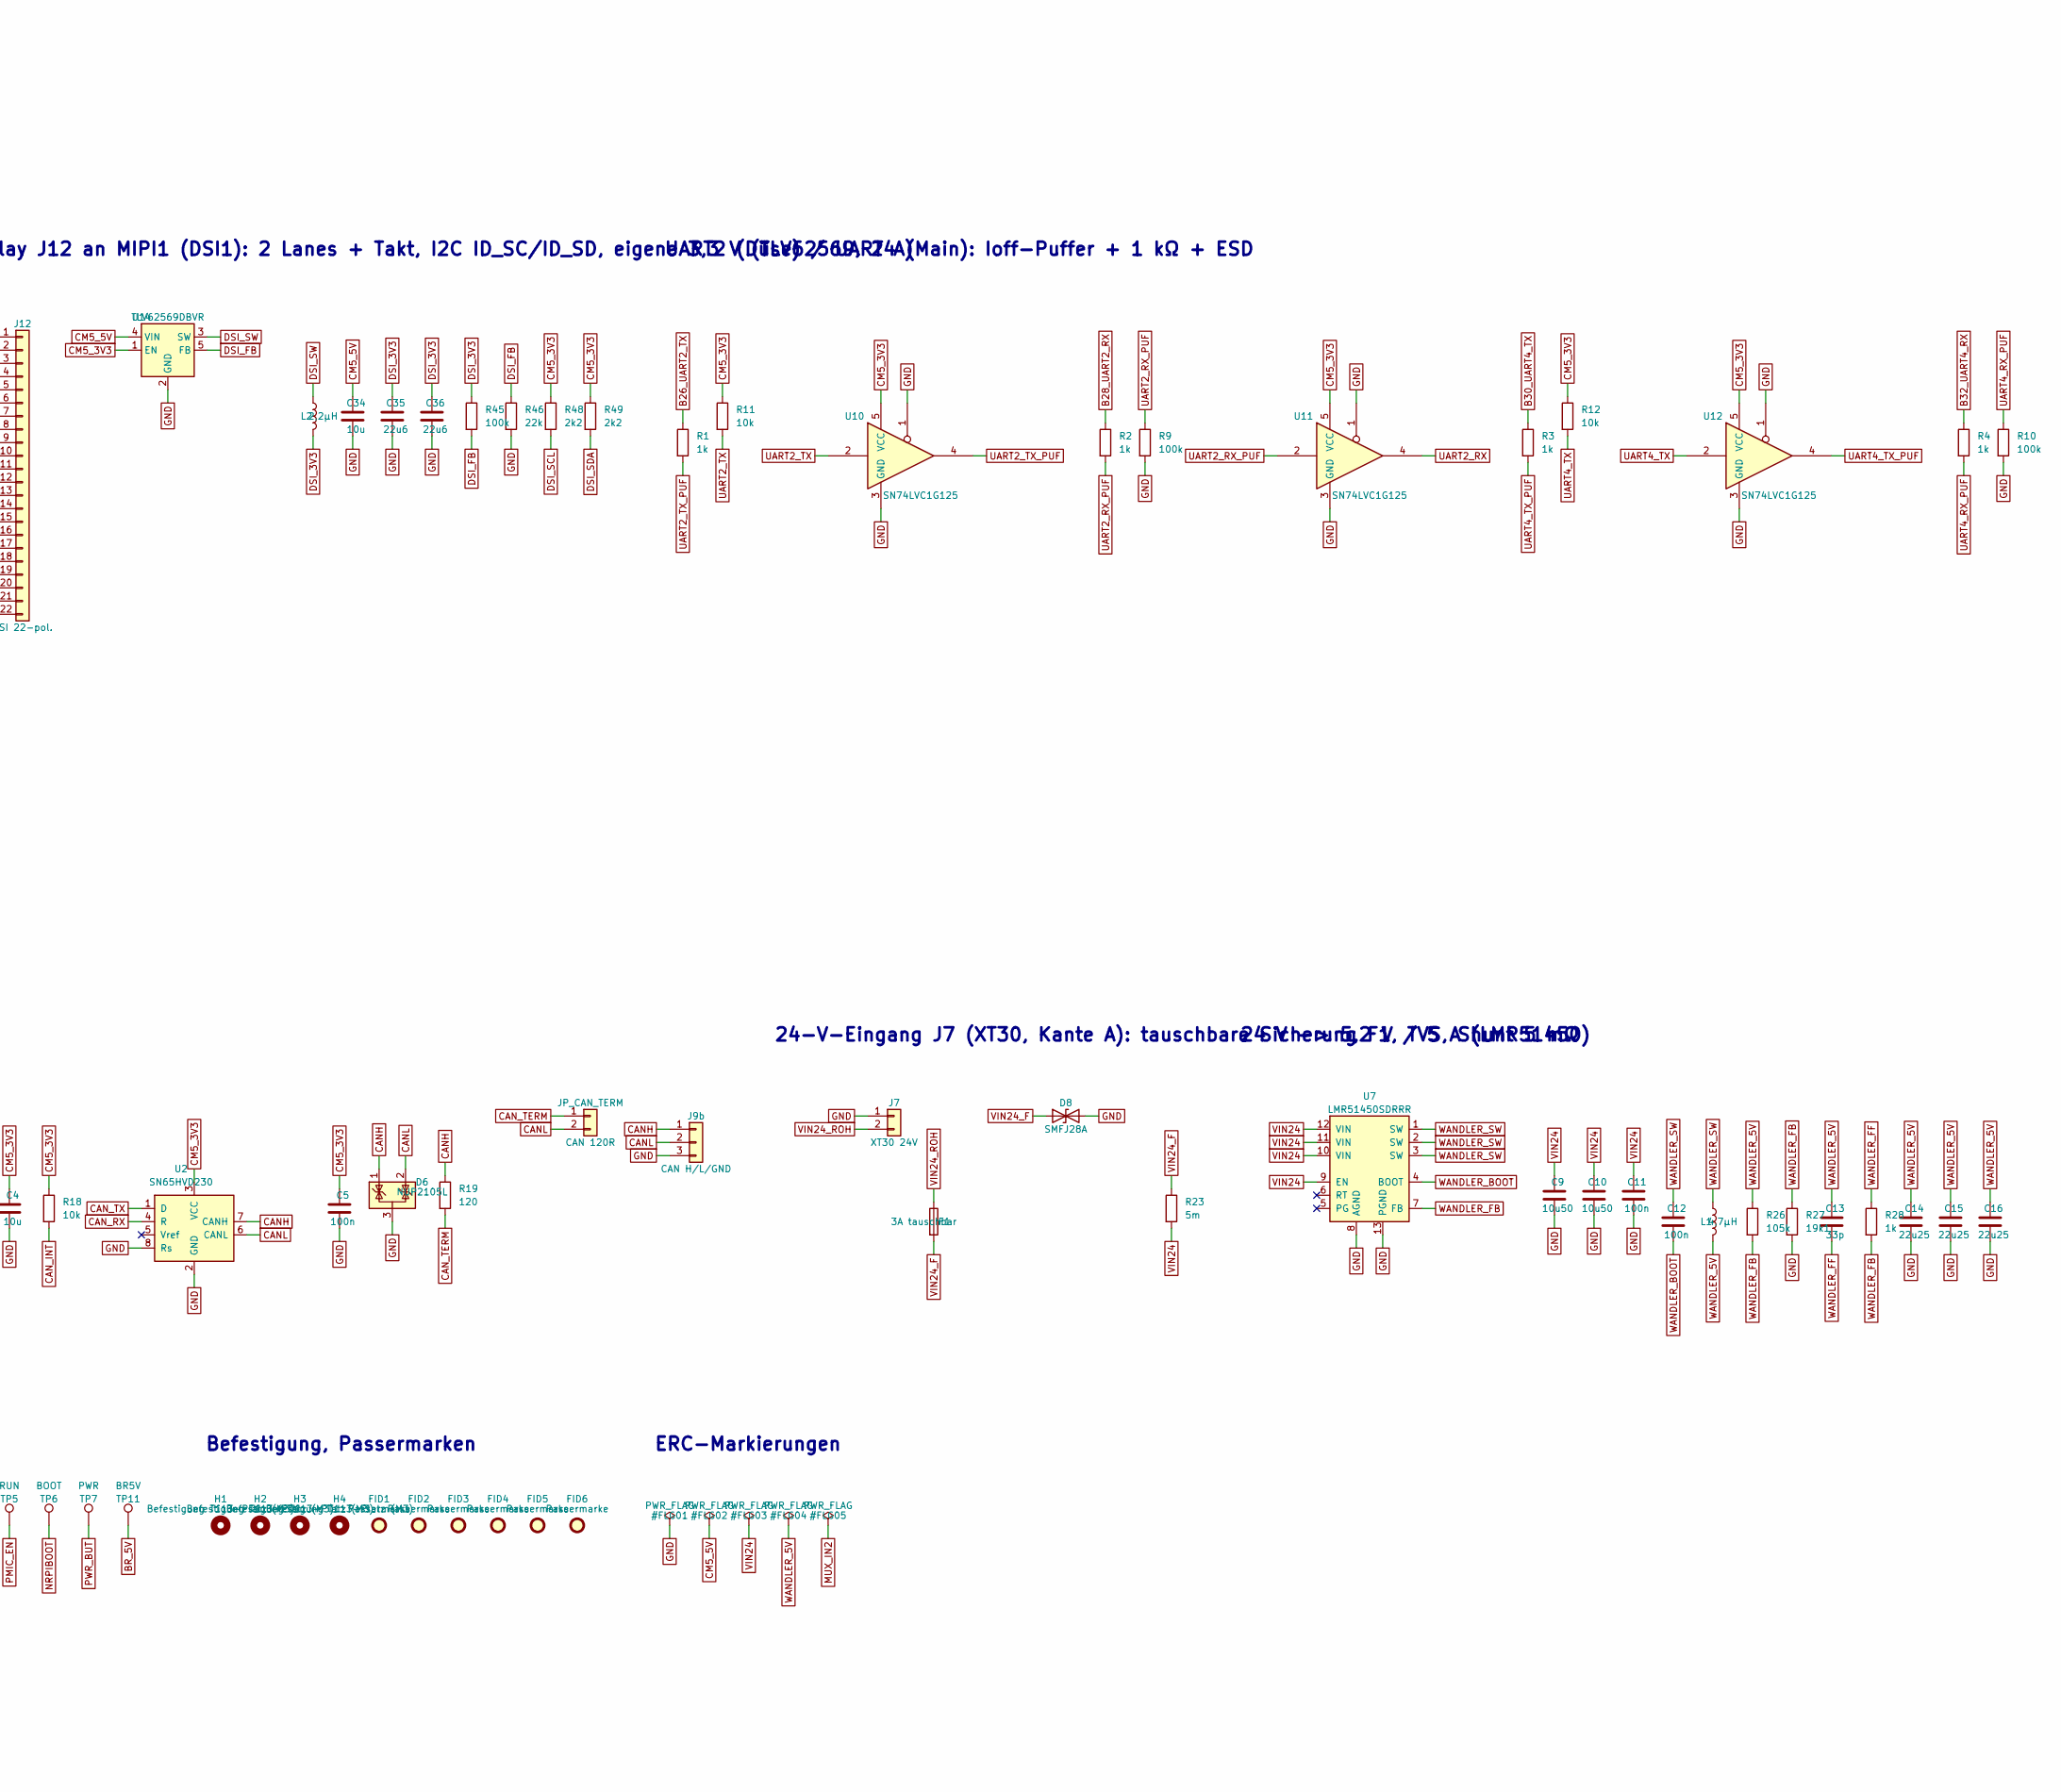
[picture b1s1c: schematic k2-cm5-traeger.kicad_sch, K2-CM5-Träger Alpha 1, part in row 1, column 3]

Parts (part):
C1, C2: 22p; C_0805_2012Metric; MPN CL21C220JBANNNC; LCSC C1804
C3, C5, C6, C7, C11, C12, C22, C25, C27, C30, C31, C32, C33: 100n; C_0805_2012Metric; MPN CC0805KRX7R9BB104; LCSC C49678
C4, C18, C34: 10u; C_0805_2012Metric; MPN CL21A106KAYNNNE; LCSC C15850
C8: 22n; C_0805_2012Metric; MPN CC0805KRX7R9BB223; LCSC C107147
C9, C10: 10u50; C_1206_3216Metric; MPN CL31A106KBHNNNE; LCSC C13585
C13: 33p; C_0805_2012Metric; MPN CC0805JRNPO9BN330; LCSC C107115
C14, C15, C16, C17, C19, C20, C21: 22u25; C_1206_3216Metric; MPN CL31A226KAHNNNE; LCSC C12891
C28: 1n2kV; C_1206_3216Metric; MPN 1206B102K202NT; LCSC C9196
C35, C36: 22u6; C_0805_2012Metric; MPN CL21A226MQQNNNE; LCSC C5674
D1, D2, D3: USBLC6-2SC6; SOT-23-6; MPN USBLC6-2SC6; LCSC C7519
D4: SRV05-4; SOT-23-6; MPN SRV05-4; LCSC C5240367
D5: SM712; SOT-23; MPN SM712; LCSC C502564
D6: NUP2105L; SOT-23; MPN NUP2105LT1G; LCSC C14486
D7: TPD4E05U06; USON-10_2.5x1.0mm_P0.5mm; MPN TPD4E05U06DQAR; LCSC C138714
D8: SMFJ28A; D_SOD-123F; MPN SMFJ28A; LCSC C5439963
D10: LED 0805 rot; LED_0805_2012Metric; MPN NCD0805R1; LCSC C84256
D11, D12, D13: LED 0805 grün; LED_0805_2012Metric; MPN KT-0805G; LCSC C2297
D14: LED 0805 gelb; LED_0805_2012Metric; MPN KT-0805Y; LCSC C2296
D15: SMF5.0A; D_SOD-123F; MPN SMF5.0A; LCSC C193402
F1: 3A tauschbar; Sicherungshalter_Littelfuse_157_Nano2_2410; MPN 0157003.DR; LCSC C187520
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
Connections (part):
B26_UART2_TX: D4.1 (IO1), J1.26, R1.1
B28_UART2_RX: D4.3 (IO2), J1.28, R2.1
B30_UART4_TX: D4.4 (IO3), J1.30, R3.1
B32_UART4_RX: D4.6 (IO4), J1.32, R4.1
BR_5V: J1.45, J1.46, J1.47, J1.48, J1.49, J1.50, R15.1, R38.1, TP11.1
CAM_DM: D1.3 (I/O2), D1.4 (I/O2), J1.37, J2.136 (USB3-0-DM)
CAM_DP: D1.1 (I/O1), D1.6 (I/O1), J1.38, J2.134 (USB3-0-DP)
CAM_GPIO0: J2.97 (CAM_GPIO0), J12.17
CAM_GPIO1: J2.100 (CAM_GPIO1), J12.18
CANH: D6.1 (K), J9b.1, R19.1, U2.7 (CANH)
CANL: D6.2 (K), J9b.2, JP_CAN_TERM.2, U2.6 (CANL)
CAN_CS: J2.39 (GPIO8), U1.13 (~CS)
CAN_INT: J2.41 (GPIO25), R18.2, U1.4 (~INT)
CAN_MISO: J2.40 (GPIO9), U1.12 (SDO)
CAN_MOSI: J2.44 (GPIO10), U1.11 (SDI)
CAN_OSC1: C1.1, U1.6 (OSC1), Y1.1
CAN_OSC2: C2.1, U1.5 (OSC2), Y1.3
CAN_RX: U1.2 (RXCAN), U2.4 (R)
CAN_SCK: J2.38 (GPIO11), U1.10 (SCK)
CAN_TERM: JP_CAN_TERM.1, R19.2
CAN_TX: U1.1 (TXCAN), U2.1 (D)
CC1_CM5: J2.94 (CC1), JP6.2 (B)
CC2_CM5: J2.96 (CC2), JP7.2 (B)
CM5_3V3: C3.1, C4.1, C5.1, C6.1, C7.1, C25.1, C30.1, C31.1, C32.1, C33.1, J2.78 (GPIO_VREF), J2.84 (CM5_3.3V), J2.86 (CM5_3.3V), R11.1, R12.1, R14.1, R18.1, R39.1, R40.1, R41.1, R42.1, R48.1, R49.1, R50.1, TP4.1, U1.14 (VDD), U2.3 (VCC), U3.8 (VCC), U4.6 (VS), U5.2 (A0), U5.6 (VS), U10.5 (VCC), U11.5 (VCC), U12.5 (VCC), U13.5 (VCC), U14.1 (EN)
CM5_5V: C19.1, C20.1, C21.1, C22.1, C34.1, J2.77 (5V), J2.79 (5V), J2.81 (5V), J2.83 (5V), J2.85 (5V), J2.87 (5V), R24.2, TP3.1, U5.8 (Vbus), U5.9 (Vin-), U14.4 (VIN)
DSI1_C_N: J2.187 (MIPI1_C_N), J12.8
DSI1_C_P: J2.189 (MIPI1_C_P), J12.9
DSI1_D0_N: J2.175 (MIPI1_D0_N), J12.2
DSI1_D0_P: J2.177 (MIPI1_D0_P), J12.3
DSI1_D1_N: J2.181 (MIPI1_D1_N), J12.5
DSI1_D1_P: J2.183 (MIPI1_D1_P), J12.6
DSI_3V3: C35.1, C36.1, J12.22, L2.2, R45.1
DSI_FB: R45.2, R46.1, U14.5 (FB)
DSI_SCL: J2.35 (ID_SC), J12.20, R48.2
DSI_SDA: J2.36 (ID_SD), J12.21, R49.2
DSI_SW: L2.1, U14.3 (SW)
ETH0_N: D7.5 (D2-), D7.6 (NC), J2.10 (Ethernet_Pair0_N), T1.6 (RD+)
ETH0_P: D7.4 (D2+), D7.7 (NC), J2.12 (Ethernet_Pair0_P), T1.8 (RD-)
ETH1_N: D7.2 (D1-), D7.9 (NC), J2.6 (Ethernet_Pair1_N), T1.3 (TD-)
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
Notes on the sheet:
GND, Spiegel 48 kein GND -> NC
GND, Spiegel 45 kein GND -> NC
5-V-Pegel – NIE anschließen
GND, Spiegel 35 kein GND -> NC
GND, Spiegel 30 kein GND -> NC
GND, Spiegel 28 kein GND -> NC
GND, Spiegel 26 kein GND -> NC
GND, Spiegel 24 kein GND -> NC
GND, Spiegel 22 kein GND -> NC
GND, Spiegel 20 kein GND -> NC
GND, Spiegel 15 kein GND -> NC
GND, Spiegel 12 kein GND -> NC
GND, Spiegel 11 kein GND -> NC
GND, Spiegel 10 kein GND -> NC
GND, Spiegel 9 kein GND -> NC
GND, Spiegel 8 kein GND -> NC
GND, Spiegel 7 kein GND -> NC
GPIO26 frei (ehem. Toolhead ~FLT)
GPIO6 frei (ehem. Toolhead-Abschaltung)
D2 (nicht verlegt)
D3 (nicht verlegt)
CM5 – beide Steckverbinder (Pin-Namen aus dem Datenblatt)
J1 – Original-Flachkabel (Pin n = Breakout n; GND nur 18/33, über PTC F3)
Ethernet – eigener 10/100-Übertrager T1 (Bridge-Board hat keinen), Bob-Smith-Abschluss, ESD
USB Kamera (USB3-0, USB2-Lane) und Hub (USB3-1, USB2-Lane) – nur J1 <-> CM5 + ESD
Notfall-USB-C J10 (stehend, OTG/rpiboot), Jumper JP_BOOT = nRPIBOOT
DSI-Display J12 an MIPI1 (DSI1): 2 Lanes + Takt, I2C ID_SC/ID_SD, eigene 3,3 V (TLV62569, 2 A)
UART2 (Düse) / UART4 (Main): Ioff-Puffer + 1 kΩ + ESD
RS485 an UART0 + DE (GPIO17), Bias/Abschluss über Lötbrücken
CAN: MCP2518FD (SPI0, INT GPIO25) + SN65HVD230
24-V-Eingang J7 (XT30, Kante A): tauschbare Sicherung F1, TVS, Shunt 5 mΩ
24 V -> 5,2 V / 5 A (LMR51450)
5-V-Power-Mux TPS2121 (Wandler vor USB-C), Shunt CM5-5V
INA226 an I2C1: 0x40 Eingang (ALERT = Stromausfall), 0x41 CM5-5V
Anzeige-LEDs
Messpunkte (Unterseite)
Befestigung, Passermarken
ERC-Markierungen
K2-CM5-Träger Alpha 1 – 23.10.2026
ALPHA – NUR FÜR TESTZWECKE – NICHT FÜR KOMMERZIELLEN EINSATZ – NUTZUNG AUF EIGENE GEFAHR

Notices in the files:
hardware/k2-pi-cm5-traeger/README.md:
SMD Pin1Right, um 90° gedreht) | KiCad-Bibliothek `kicad-library-3d` 10.0.7 (`${KICAD10_3DMODEL_DIR}`, Renders setzen die Variable in `bauen.sh`) | **CC-BY-SA 4.0 mit Ausnahme** (Verwendung in eigenen Designs frei, Modelle selbst nicht im Repo)
